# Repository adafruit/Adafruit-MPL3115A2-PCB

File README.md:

# Adafruit MPL3115A2 I2C Barometric Pressure/Altitude/Temperature Sensor PCB
<a href="http://www.adafruit.com/products/1893"><br/>
Click here to purchase one from the Adafruit shop</a>

This pressure sensor from Freescale is a great low-cost sensing solution for precision measurement of barometric pressure and altitude. The MPL3115A2 has a typical 1.5 Pascal resolution, which can resolve altitude at 0.3 meters (compare to the BMP180 which can do 0.17m). It has some upsides compared to the BMP280, such as interrupt outputs for ultra-low power usage, and its also a heck of a lot easier to read altitude with a built in altimeter calculation - no calibration reading and calculating required. As a bonus, there's even a fairly good temperature sensor with ±1°C typical accuracy (±3°C max).

These are the Eagle CAD files for the Adafruit MPL3115A2 Barometric 
Pressure/Temperature/Altitude Sensor
. 
For more details, check out the product page at

-----> https://www.adafruit.com/product/1893

### License

Adafruit invests time and resources providing this open source design, please support Adafruit and open-source hardware by purchasing products from [Adafruit](https://www.adafruit.com)!

All text above must be included in any redistribution

Designed by Limor Fried/Ladyada for Adafruit Industries.
Creative Commons Attribution/Share-Alike, all text above must be included in any redistribution. 
See license.txt for additional information.

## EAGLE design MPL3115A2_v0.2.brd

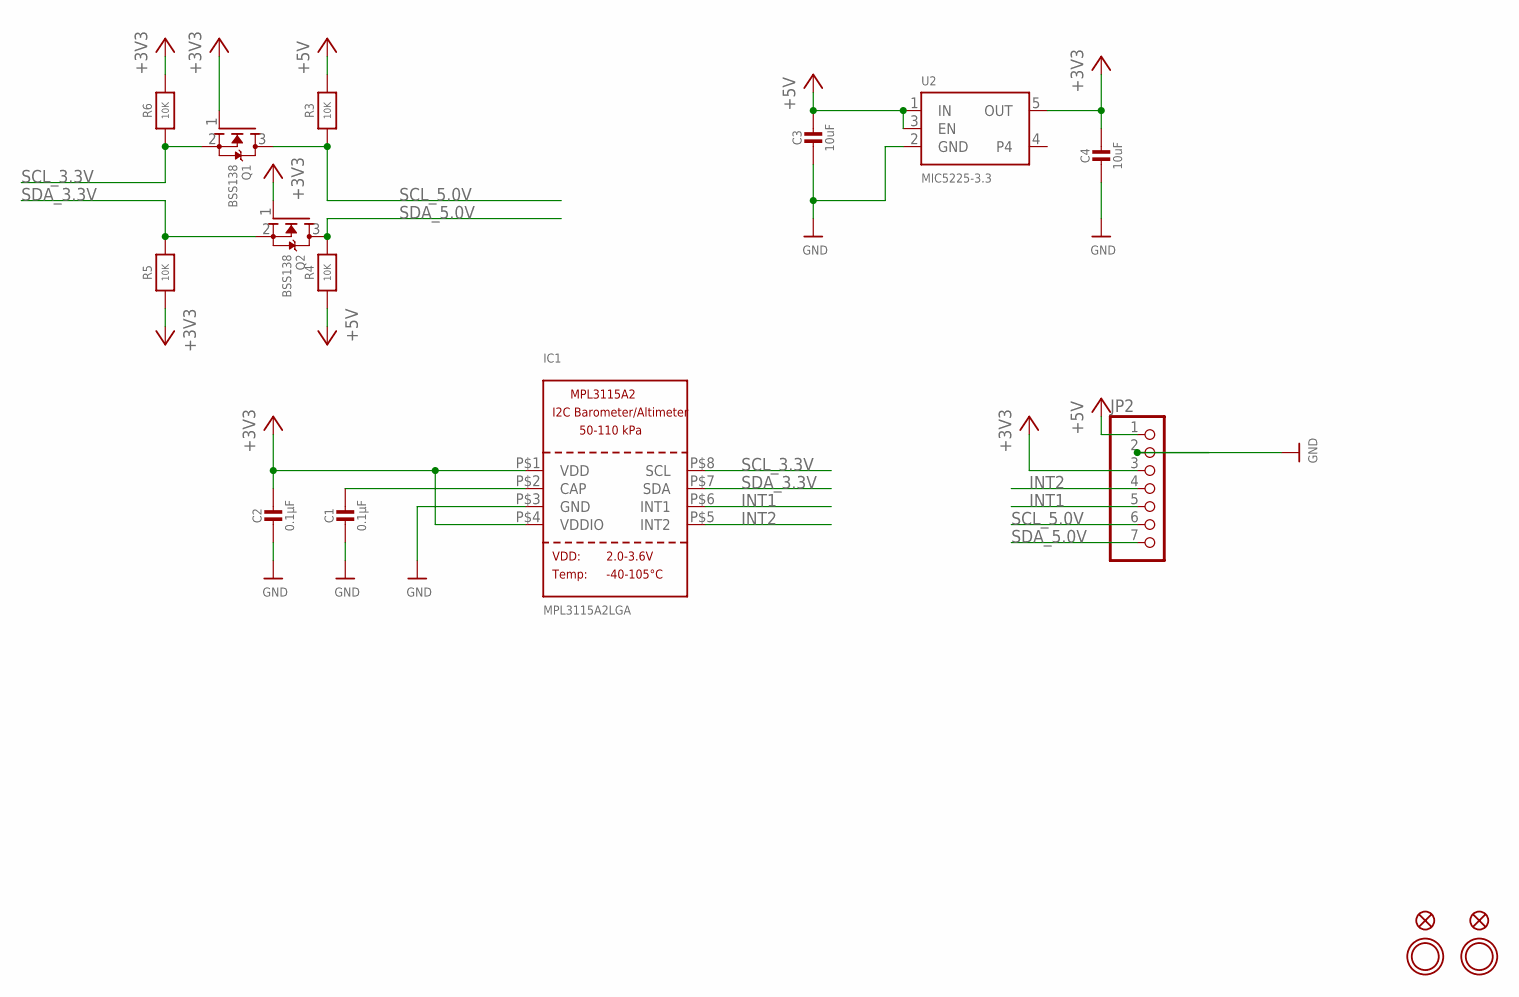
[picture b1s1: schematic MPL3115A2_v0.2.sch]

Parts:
C1, C2: 0.1µF; 0805-NO
C3, C4: 10uF; 0805-NO
FID1, FID2: FIDUCIAL""; FIDUCIAL_1MM
IC1: MPL3115A2LGA; LGA8
JP2: HEADER-1X770MIL; 1X07_ROUND_70
Q1, Q2: BSS138; SOT23-WIDE
R3, R4, R5, R6: 10K; 0805-NO
U2: MIC5225-3.3; SOT23-5
U$8, U$9: MOUNTINGHOLE2.5; MOUNTINGHOLE_2.5_PLATED

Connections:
+3V3: C2.1, C4.1, IC1.P$1 (VDD), IC1.P$4 (VDDIO), JP2.3, Q1.1 (G), Q2.1 (G), R5.1, R6.2, U2.5 (OUT)
+5V: C3.1, JP2.1, R3.2, R4.1, U2.1 (IN), U2.3 (EN)
CAP: C1.1, IC1.P$2 (CAP)
GND: C1.2, C2.2, C3.2, C4.2, IC1.P$3 (GND), JP2.2, U2.2 (GND)
INT1: IC1.P$6 (INT1), JP2.5
INT2: IC1.P$5 (INT2), JP2.4
SCL_3.3V: IC1.P$8 (SCL), Q1.2 (S), R6.1
SCL_5.0V: JP2.6, Q1.3 (D), R3.1
SDA_3.3V: IC1.P$7 (SDA), Q2.2 (S), R5.2
SDA_5.0V: JP2.7, Q2.3 (D), R4.2

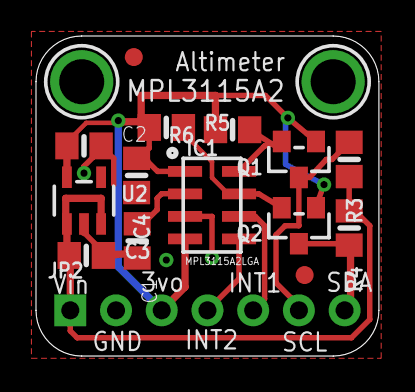
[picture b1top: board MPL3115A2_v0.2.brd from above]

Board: 2 copper layers, 19.1 x 17.8 mm, 18 parts (1 on the bottom side), 10 nets.

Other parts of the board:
U$14: ADAFRUIT_3.5MM

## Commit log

2014-12-16 init
